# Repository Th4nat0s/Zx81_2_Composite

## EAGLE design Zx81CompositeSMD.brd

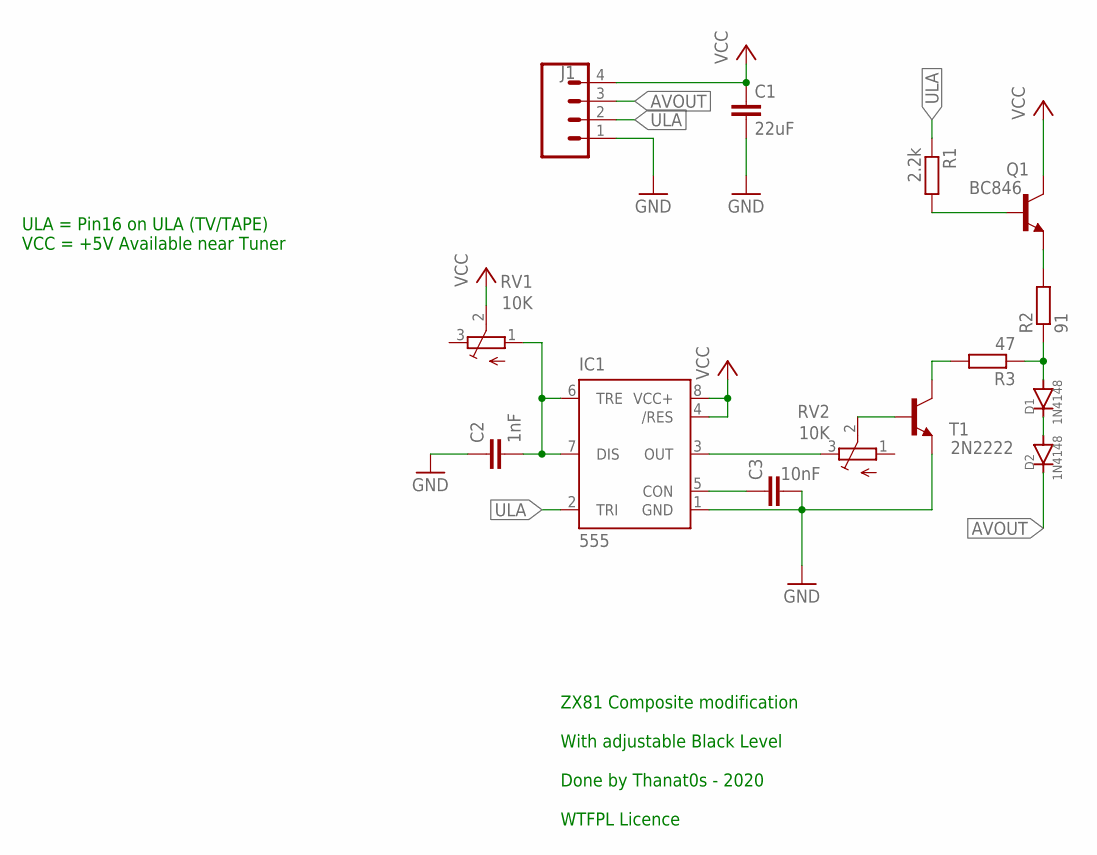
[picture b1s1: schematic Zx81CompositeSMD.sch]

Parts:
C1: 22uF; C1206K
C2: 1nF; C0603K
C3: 10nF; C0603K
D1, D2: 1N4148; SOD-323
IC1: 555; SO08
J1: CONN_04; 1X04
Q1: BC846; SOT23
R1: 2.2k; R0603
R2: 91; R0603
R3: 47; R0603
RV1, RV2: 10K; SM-42/43A
T1: 2N2222; SOT23

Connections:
AVOUT: D2.C, J1.3
GND: C1.2, C2.1, C3.2, IC1.1 (GND), J1.1, T1.2 (E)
unnamed: Q1.1 (B), R1.2
unnamed: D1.C, D2.A
unnamed: RV2.2 (S), T1.1 (B)
unnamed: C3.1, IC1.5 (CON)
unnamed: C2.2, IC1.6 (TRE), IC1.7 (DIS), RV1.1 (A)
unnamed: IC1.3 (OUT), RV2.3 (E)
unnamed: D1.A, R2.1, R3.1
unnamed: R3.2, T1.3 (C)
unnamed: Q1.2 (E), R2.2
ULA: IC1.2 (TRI), J1.2, R1.1
VCC: C1.1, IC1.4 (/RES), IC1.8 (VCC+), J1.4, Q1.3 (C), RV1.2 (S)

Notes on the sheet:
ZX81 Composite modification With adjustable Black Level Done by Thanat0s - 2020 WTFPL Licence
ULA = Pin16 on ULA (TV/TAPE) VCC = +5V Available near Tuner

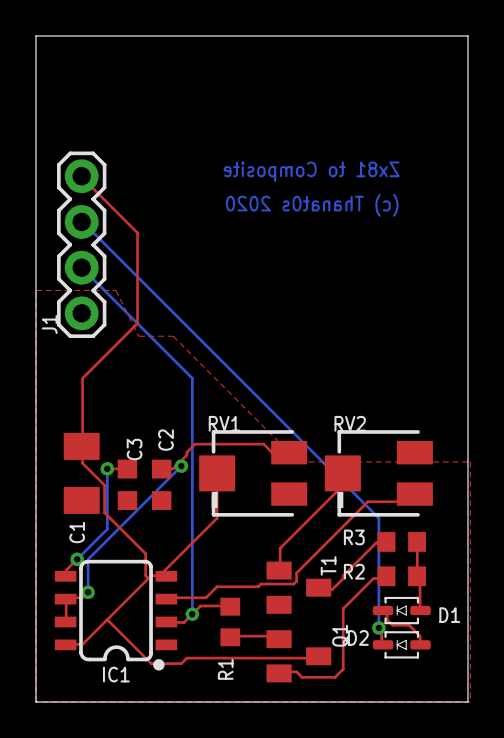
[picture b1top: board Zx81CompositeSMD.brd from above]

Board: 2 copper layers, 24.0 x 37.0 mm, 14 parts (0 on the bottom side), 13 nets.

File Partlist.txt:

Partlist

Exported from Zx81Composite.sch at 13/04/2020 15:49

EAGLE Version 9.6.1 Copyright (c) 1988-2020 Autodesk, Inc.

Assembly variant: 

Part     Value          Device          Package       Library                      Sheet

C1       22uF           CPOL-EUE2.5-5   E2,5-5        rcl                          1
C2       1nF            C-EU025-024X044 C025-024X044  rcl                          1
C3       10nF           C-EU025-024X044 C025-024X044  rcl                          1
D1       1N4148         1N4148DO35-7    DO35-7        diode                        1
D2       1N4148         1N4148DO35-7    DO35-7        diode                        1
IC1      555            555P            DIP08         SparkFun-IC-Special-Function 1
J1                      CONN_04         1X04          SparkFun-Connectors          1
Q1       BC548          BC548           TO92-EBC      transistor-npn               1
R1       2.2k           R-EU_0207/7     0207/7        rcl                          1
R2       91             R-EU_0207/7     0207/7        rcl                          1
R3       47             R-EU_0207/7     0207/7        rcl                          1
RV1      10K            TRIM_EU-CA6V    CA6V          pot                          1
RV2      10K            TRIM_EU-CA6V    CA6V          pot                          1
T1       2N2222         2N2222          TO92-EBC-OVAL adafruit                     1

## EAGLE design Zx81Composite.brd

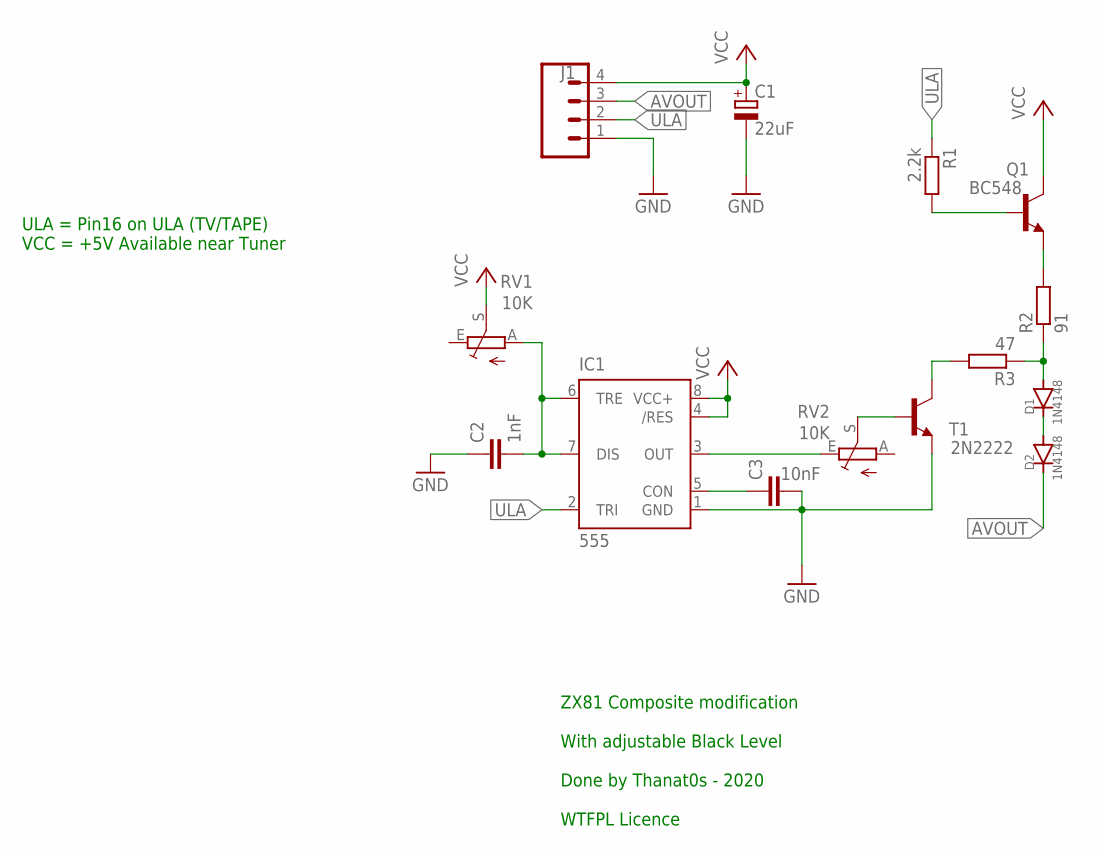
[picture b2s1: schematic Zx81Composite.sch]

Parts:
C1: 22uF; E2,5-5
C2: 1nF; C025-024X044
C3: 10nF; C025-024X044
D1, D2: 1N4148; DO35-7
IC1: 555; DIP08
J1: CONN_04; 1X04
Q1: BC548; TO92-EBC
R1: 2.2k; 0207/7
R2: 91; 0207/7
R3: 47; 0207/7
RV1, RV2: 10K; CA6V
T1: 2N2222; TO92-EBC-OVAL

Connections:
AVOUT: D2.C, J1.3
GND: C1.-, C2.1, C3.2, IC1.1 (GND), J1.1, T1.E
unnamed: Q1.B, R1.2
unnamed: D1.C, D2.A
unnamed: RV2.S, T1.B
unnamed: C3.1, IC1.5 (CON)
unnamed: C2.2, IC1.6 (TRE), IC1.7 (DIS), RV1.A
unnamed: IC1.3 (OUT), RV2.E
unnamed: D1.A, R2.1, R3.1
unnamed: R3.2, T1.C
unnamed: Q1.E, R2.2
ULA: IC1.2 (TRI), J1.2, R1.1
VCC: C1.+, IC1.4 (/RES), IC1.8 (VCC+), J1.4, Q1.C, RV1.S

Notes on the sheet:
ZX81 Composite modification With adjustable Black Level Done by Thanat0s - 2020 WTFPL Licence
ULA = Pin16 on ULA (TV/TAPE) VCC = +5V Available near Tuner

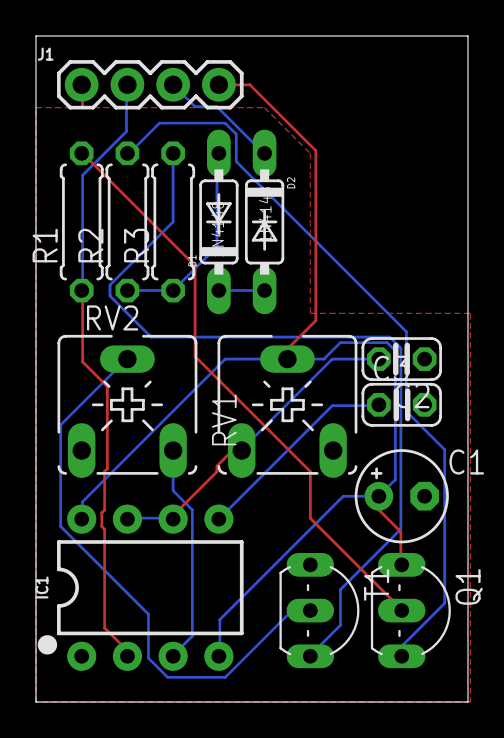
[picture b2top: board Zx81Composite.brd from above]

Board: 2 copper layers, 24.0 x 37.0 mm, 14 parts (0 on the bottom side), 13 nets.

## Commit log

2020-04-11 Initial Version
2020-04-11 Add Oscillo Pictures
2020-04-13 Change implementation
2020-04-15 Ready smd

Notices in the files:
parts and their libraries:
SparkFun-IC-Special-Function: Licensing: Creative Commons ShareAlike 4.0 International - https://creativecommons.org/licenses/by-sa/4.0
